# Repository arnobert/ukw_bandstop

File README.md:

# ukw_bandstop
## Bandstop filter on a small PCB to eliminate strong VHF FM radio (87.5 - 108 MHz) broadcast signals.

FM radio broadcast signals are usually really strong compared to e.g. ham radio short wave signals. The FM signals can cause massive intermodulation in SDRs, LimeSDR in my case. So I designed a small prototype of a filter for these frequencies.

### Calculation
I used the free version of Ansoft Designer for the calculation of the filter. Parameters were:
* Legendre approximation
* Stop band from 80 to 120 MHz
* Order 5

After calculation I had to tune/round the values of Cs and Ls to existing components.

### PCB design
The input and output are SMA connectors. All other components are 0603 SMD.

### First prototype
The first prototype was ordered at dirtypcbs. 

### Results
I soldered one board and measured with my Siglent SSA 3021X spectrum analyzer, see screenshot. 
You can see the corner frequencies at 73 and 140 MHz.

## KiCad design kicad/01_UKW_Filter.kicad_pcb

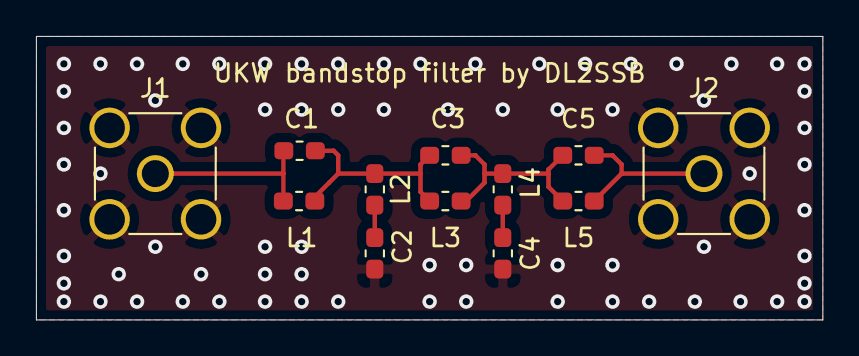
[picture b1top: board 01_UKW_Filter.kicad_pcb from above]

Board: 2 copper layers, 43.7 x 15.7 mm, 12 parts (0 on the bottom side), 7 nets.

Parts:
C1: 82pF; C_0603_1608Metric_Pad1.05x0.95mm_HandSolder
C2, C4: 20pF; C_0603_1608Metric_Pad1.05x0.95mm_HandSolder
C3, C5: 39pF; C_0603_1608Metric_Pad1.05x0.95mm_HandSolder
J1, J2: Conn_Coaxial; SMA_Amphenol_901-144_Vertical
L1: 27nH; L_0603_1608Metric_Pad1.05x0.95mm_HandSolder
L2, L4: 140nH; L_0603_1608Metric_Pad1.05x0.95mm_HandSolder
L3, L5: 68nH; L_0603_1608Metric_Pad1.05x0.95mm_HandSolder

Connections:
GND: C2.1, C4.1, J1.2, J2.2
unnamed: C1.1, C3.2, L1.2, L2.1, L3.1
unnamed: C1.2, J1.1, L1.1
unnamed: C2.2, L2.2
unnamed: C3.1, C5.2, L3.2, L4.1, L5.1
unnamed: C4.2, L4.2
unnamed: C5.1, J2.1, L5.2

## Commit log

2020-11-04 Add measurement
2020-11-04 Added kicad sources
2020-11-04 Added Ansoft Designer file
2020-11-04 Wrote Readme
2020-11-22 Added schematic png
